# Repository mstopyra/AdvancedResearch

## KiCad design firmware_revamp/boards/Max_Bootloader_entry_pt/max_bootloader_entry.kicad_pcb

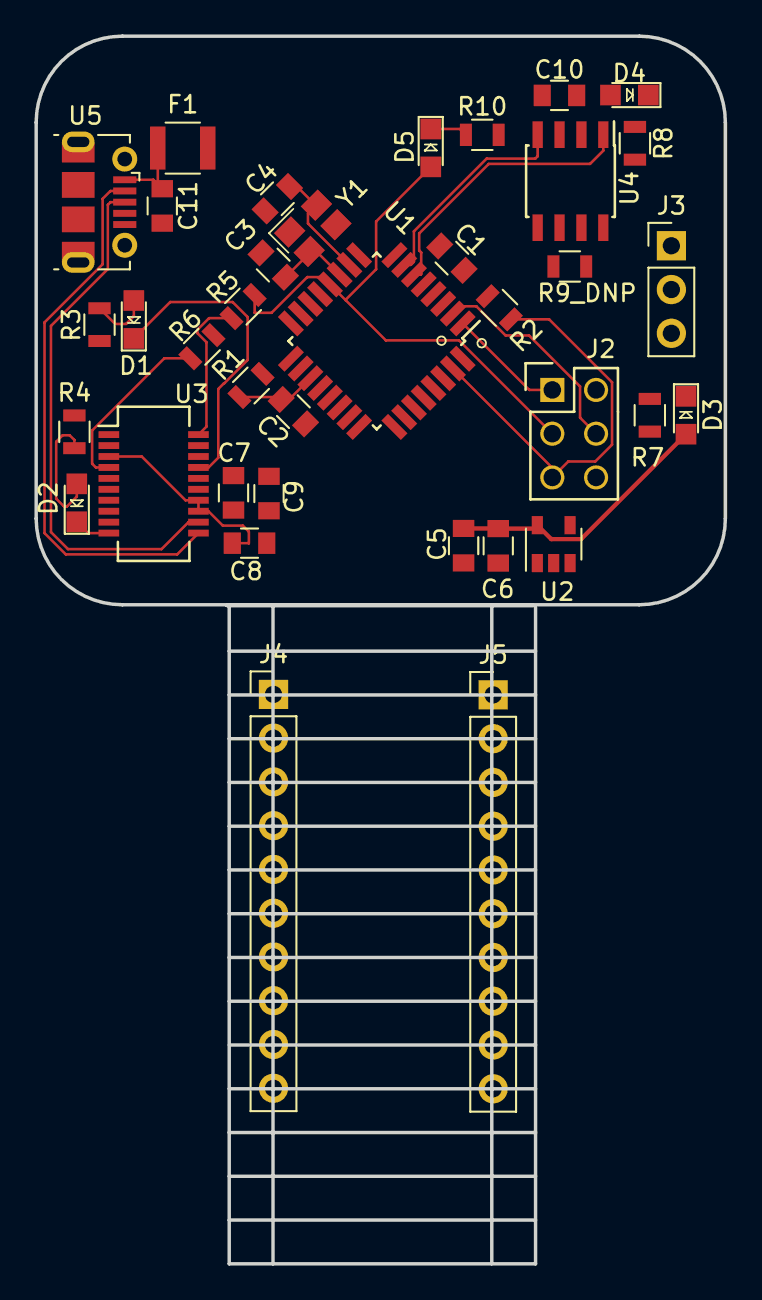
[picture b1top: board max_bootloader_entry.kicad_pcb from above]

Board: 2 copper layers, 40.0 x 71.3 mm, 37 parts (0 on the bottom side), 27 nets.

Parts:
C1, C6, C7, C8, C10, C11: C_0.1uF; C_0805_OEM
C2: C_100pF; C_0805_OEM
C3, C4: C_30pF; C_0805_OEM
C5, C9: C_10uF; C_0805_OEM
D1: Rx_LED; LED_0805_OEM
D2: Tx_LED; LED_0805_OEM
D3: 3V3_LED; LED_0805_OEM
D4: 5V_LED; LED_0805_OEM
D5: SCK_LED; LED_0805_OEM
F1: F_500mA_16V; Fuse_1210
J2: CONN_02X03; Pin_Header_Straight_2x03
J3: CONN_01X03; PinHeader_1x03_P2.54mm_Vertical
J4, J5: Conn_01x10; PinHeader_1x10_P2.54mm_Vertical
R1: R_100; R_0805_OEM
R2: R_10K; R_0805_OEM
R3, R4, R5, R6, R7, R8, R10: R_1K; R_0805_OEM
R9_DNP: R_120_DNP; R_0805_OEM
U1: ATMEGA16M1; TQFP-32_7x7mm_Pitch0.8mm
U2: MIC5205-3.3YM5; SOT-23-5
U3: FT231XS; SSOP-20_3.9x8.7mm_P0.635mm
U4: MCP2561-E_SN; SOIC-8_3.9x4.9mm_Pitch1.27mm_OEM
U5: USB_MicroB; USB_Micro-B_Molex-105017-0001
Y1: Crystal_SMD; Crystal_SMD_FA238

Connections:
+3V3: C5.1, C6.1, D3.2, U2.5
+5V: C1.1, C7.1, C9.1, C10.1, D4.2, F1.1, J2.2, R1.1, R2.1, R3.2, R4.2, U1.4, U2.1, U2.3, U3.15, U4.3
/3V3_FTDI: C8.1, U3.3, U3.13, U3.14
/CAN_+: J3.1, R9_DNP.1, U4.7
/CAN_-: J3.2, R9_DNP.2, U4.6
/CAN_RX: U1.7, U4.4
/CAN_TX: U1.6, U4.1
/MISO: J2.1, U1.1
/MOSI: J2.4, R6.2, U1.2
/RESET: J2.5, R2.2, U1.31
/SCK: D5.2, J2.3, R5.2, U1.12
/USBD+: U3.11, U5.2
/USBD-: U3.12, U5.3
GND: C1.2, C2.2, C3.2, C4.2, C5.2, C6.2, C7.2, C8.2, C9.2, C10.2, C11.2, J2.6, J3.3, R7.2, R8.2, R10.2, U1.5, U1.20, U2.2, U3.6, U3.16, U4.2, U4.8, U5.5, U5.6, Y1.2, Y1.4
unnamed: C2.1, R1.2, U1.19
unnamed: C3.1, U1.11, Y1.1
unnamed: C4.1, U1.10, Y1.3
unnamed: C11.1, F1.2, U5.1
unnamed: D1.1, U3.17
unnamed: D1.2, R3.1
unnamed: D2.1, U3.10
unnamed: D2.2, R4.1
unnamed: D3.1, R7.1
unnamed: D4.1, R8.1
unnamed: D5.1, R10.1
unnamed: R5.1, U3.20
unnamed: R6.1, U3.4

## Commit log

2021-04-02 Made progress on layout.
2021-04-15 Work on bootloader board after first pass
2021-04-16 What I have so far on bootloader board
